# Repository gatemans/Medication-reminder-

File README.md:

# Medication-reminder-
An embedded hardware solution for managing medication schedules and reminding users to take their medicines

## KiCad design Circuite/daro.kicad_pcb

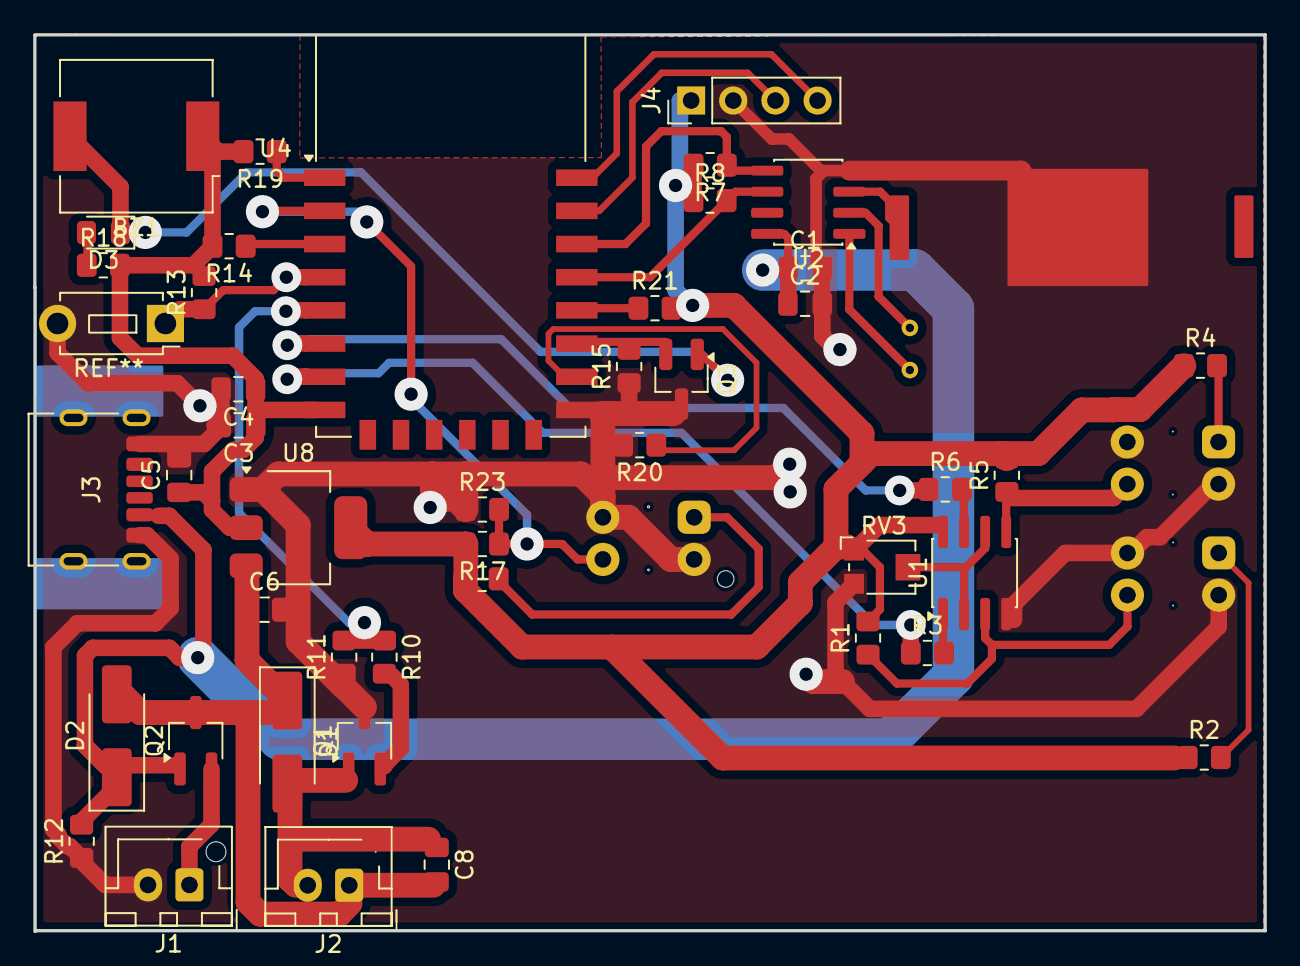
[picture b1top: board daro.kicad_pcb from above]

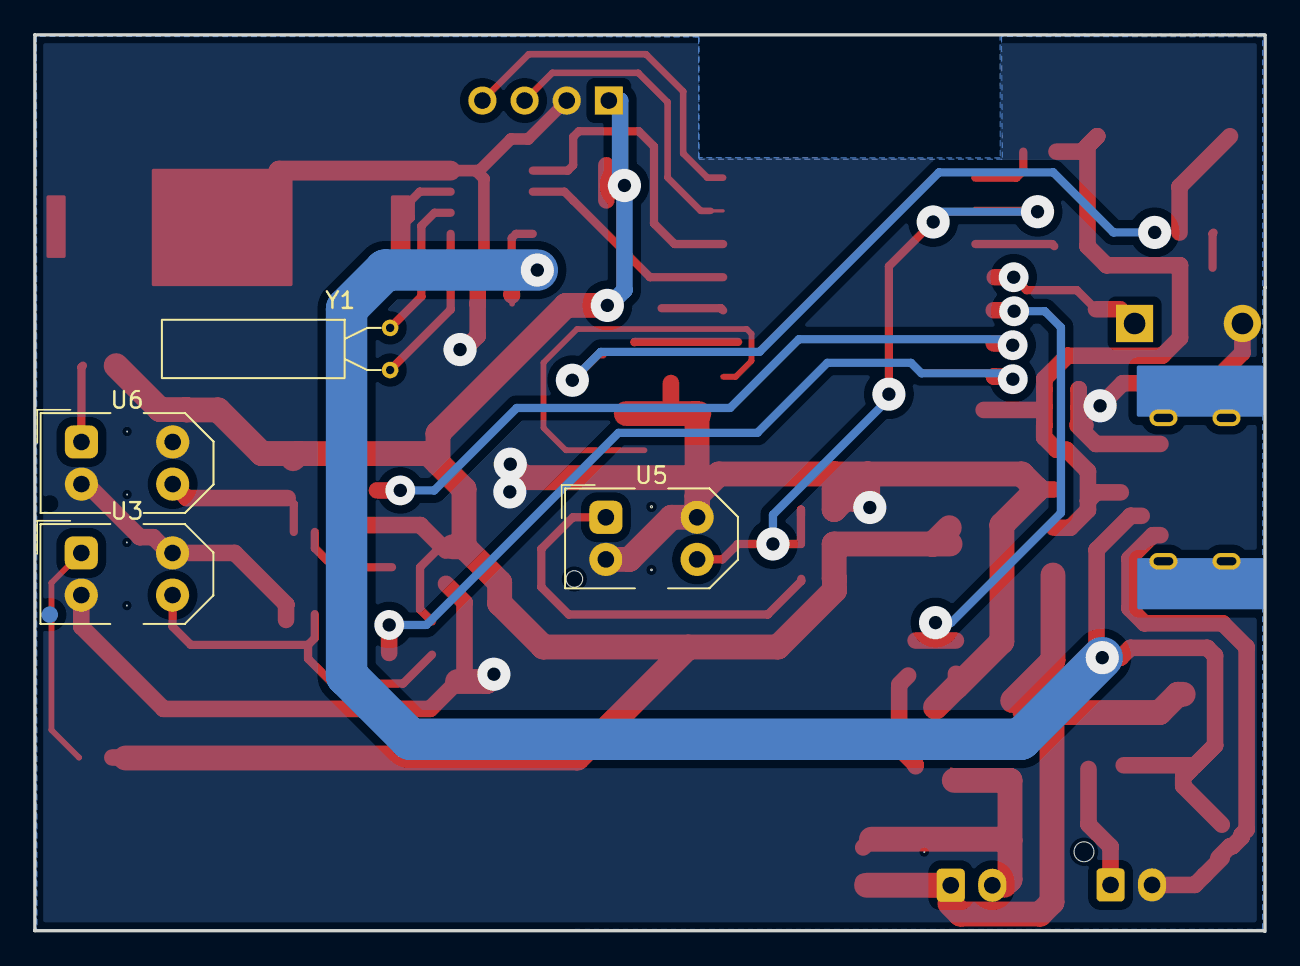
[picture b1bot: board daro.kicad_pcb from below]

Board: 2 copper layers, 74.2 x 54.0 mm, 48 parts (4 on the bottom side), 33 nets.

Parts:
BZ1: Buzzer; Buzzer_CUI_CPT-9019S-SMT
C1, C3: 100nF; C_0805_2012Metric_Pad1.18x1.45mm_HandSolder
C2, C4, C5, C6, C8: 10uF; C_0805_2012Metric_Pad1.18x1.45mm_HandSolder
D1: MRA4007T3G; D_SMA_Handsoldering
D2: SS36; D_SMA_Handsoldering
D3: LED; LED_0805_2012Metric_Pad1.15x1.40mm_HandSolder
J1, J2: Conn_01x02_Socket; JST_XH_B2B-XH-AM_1x02_P2.50mm_Vertical
J3: USB_C_Receptacle_PowerOnly_6P; USB_C_Receptacle_HRO_TYPE-C-31-M-17
J4: Conn_01x04_Socket; PinHeader_1x04_P2.54mm_Vertical
Q1: AO3400A; SOT-23W_Handsoldering
Q2: AO3407A; SOT-23W_Handsoldering
Q3: 2N7002H; SOT-23_Handsoldering
R1, R3, R5, R6, R7, R8, R11, R12, R13, R14, R15, R19, R20, R21, R23: 10K; R_0805_2012Metric_Pad1.20x1.40mm_HandSolder
R2, R4, R10, R16, R18: 150; R_0805_2012Metric_Pad1.20x1.40mm_HandSolder
R17: 47K; R_0805_2012Metric_Pad1.20x1.40mm_HandSolder
RV3: R_Potentiometer; Potentiometer_Bourns_TC33X_Vertical
U1: LM393; SOIC-8_3.9x4.9mm_P1.27mm
U2: DS1307Z+; SOIC-8_3.9x4.9mm_P1.27mm
U3, U5, U6: TCRT5000; Vishay_TCRT5000
U4: ESP-12F; ESP-12E
U8: AMS1117-3.3; SOT-223-3_TabPin2
Y1: Crystal; Crystal_AT310_D3.0mm_L10.0mm_Horizontal

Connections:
+3.3V: BZ1.1 (+), C3.1, C4.1, C5.1, J4.1, R1.2, R2.1, R4.1, R5.2, R7.2, R8.1, R13.2, R14.2, R16.1, R17.2, R18.2, R19.2, R21.2, RV3.1, U1.8 (V+), U4.8 (VCC), U8.2 (VO)
+5V: C1.1, C2.1, D2.1 (K), J3.A9 (VBUS), J3.B9 (VBUS), Q2.1 (G), R12.2, U2.8 (VCC)
ADC: R17.1, R23.2, U4.2 (ADC), U5.3 (COLL)
GND: C1.2, C2.2, C3.2, C4.2, C5.2, C6.2, J1.2, J3.A12 (GND), J3.B12 (GND), J4.2, Q1.3 (D), Q3.3 (D), R11.1, R12.1, R15.1, R20.2, R23.1, RV3.3, U1.4 (V-), U2.4 (GND), U3.2 (CATH), U3.4 (E), U4.15 (GND), U5.2 (CATH), U5.4 (E), U6.2 (CATH), U6.4 (E), U8.1 (GND)
unnamed: BZ1.2 (-), D3.1 (K), Q3.1 (G)
unnamed: C8.1, D1.2 (A), J2.2, Q1.1 (G)
unnamed: D3.2 (A), R18.1
unnamed: J1.1, Q2.2 (S)
unnamed: Q1.2 (S), R10.2
unnamed: R3.2, U1.1
unnamed: R6.2, U1.7
unnamed: U2.1 (X1), Y1.2
unnamed: U2.2 (X2), Y1.1
unnamed: R2.2, U3.1 (A)
unnamed: R14.1, U4.3 (EN)
unnamed: R21.1, U4.18 (GPIO0)
unnamed: R20.1, U4.16 (GPIO15)
unnamed: R19.1, U4.1 (~RST)
unnamed: R16.2, U5.1 (A)
unnamed: R4.2, U6.1 (A)
RX: J4.3, U4.21 (GPIO3/RXD)
TX: J4.4, U4.22 (GPIO1/TXD)
Vin: C6.1, C8.2, D1.1 (K), D2.2 (A), J2.1, Q2.3 (D), U8.3 (VI)
apm3: R1.1, U1.3 (+), U3.3 (COLL)
apm5: R5.1, U1.5 (+), U6.3 (COLL)
io2: Q3.2 (S), R15.2, U4.17 (GPIO2)
io4: R8.2, U2.6 (SCL), U4.19 (GPIO4)
io5: R7.1, U2.5 (SDA), U4.20 (GPIO5)
io12: R6.1, U4.6 (GPIO12)
io13: R3.1, U4.7 (GPIO13)
io14: R10.1, R11.2, U4.5 (GPIO14)
io16: R13.1, U4.4 (GPIO16)
pot: RV3.2, U1.2 (-), U1.6 (-)
